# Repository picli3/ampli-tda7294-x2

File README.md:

# ampli-tda7294-x2

Amplificador de audio basado en **dos TDA7294**, pensado como una solución práctica para construir una etapa estéreo de potencia usando un integrado muy conocido en audio DIY.

## Propósito del proyecto
Este repositorio reúne el diseño electrónico y mecánico de una placa orientada a implementar un amplificador con **dos canales**, usando el TDA7294 como núcleo de cada etapa.

La idea principal del proyecto es ofrecer una base para:
- construir un amplificador estéreo
- reutilizar una topología conocida y fácil de conseguir
- integrar PCB, esquemático y soporte mecánico/disipación
- facilitar prototipado o fabricación de una etapa de audio casera o semiprofesional

## Qué incluye
- esquemáticos del amplificador
- diseño PCB en KiCad
- documentación exportada en PDF/HTML
- archivos mecánicos del disipador o soporte en FreeCAD

## Enfoque técnico
El TDA7294 es un integrado muy usado en amplificadores de audio por su simplicidad de implementación y buena potencia para aplicaciones domésticas, educativas o DIY. En este proyecto se usa por duplicado, lo que permite montar una etapa de dos canales sobre una misma base de diseño.

## Aplicaciones típicas
- amplificador estéreo DIY
- sistema de audio casero
- etapa de potencia para pruebas de laboratorio
- proyecto educativo de audio analógico

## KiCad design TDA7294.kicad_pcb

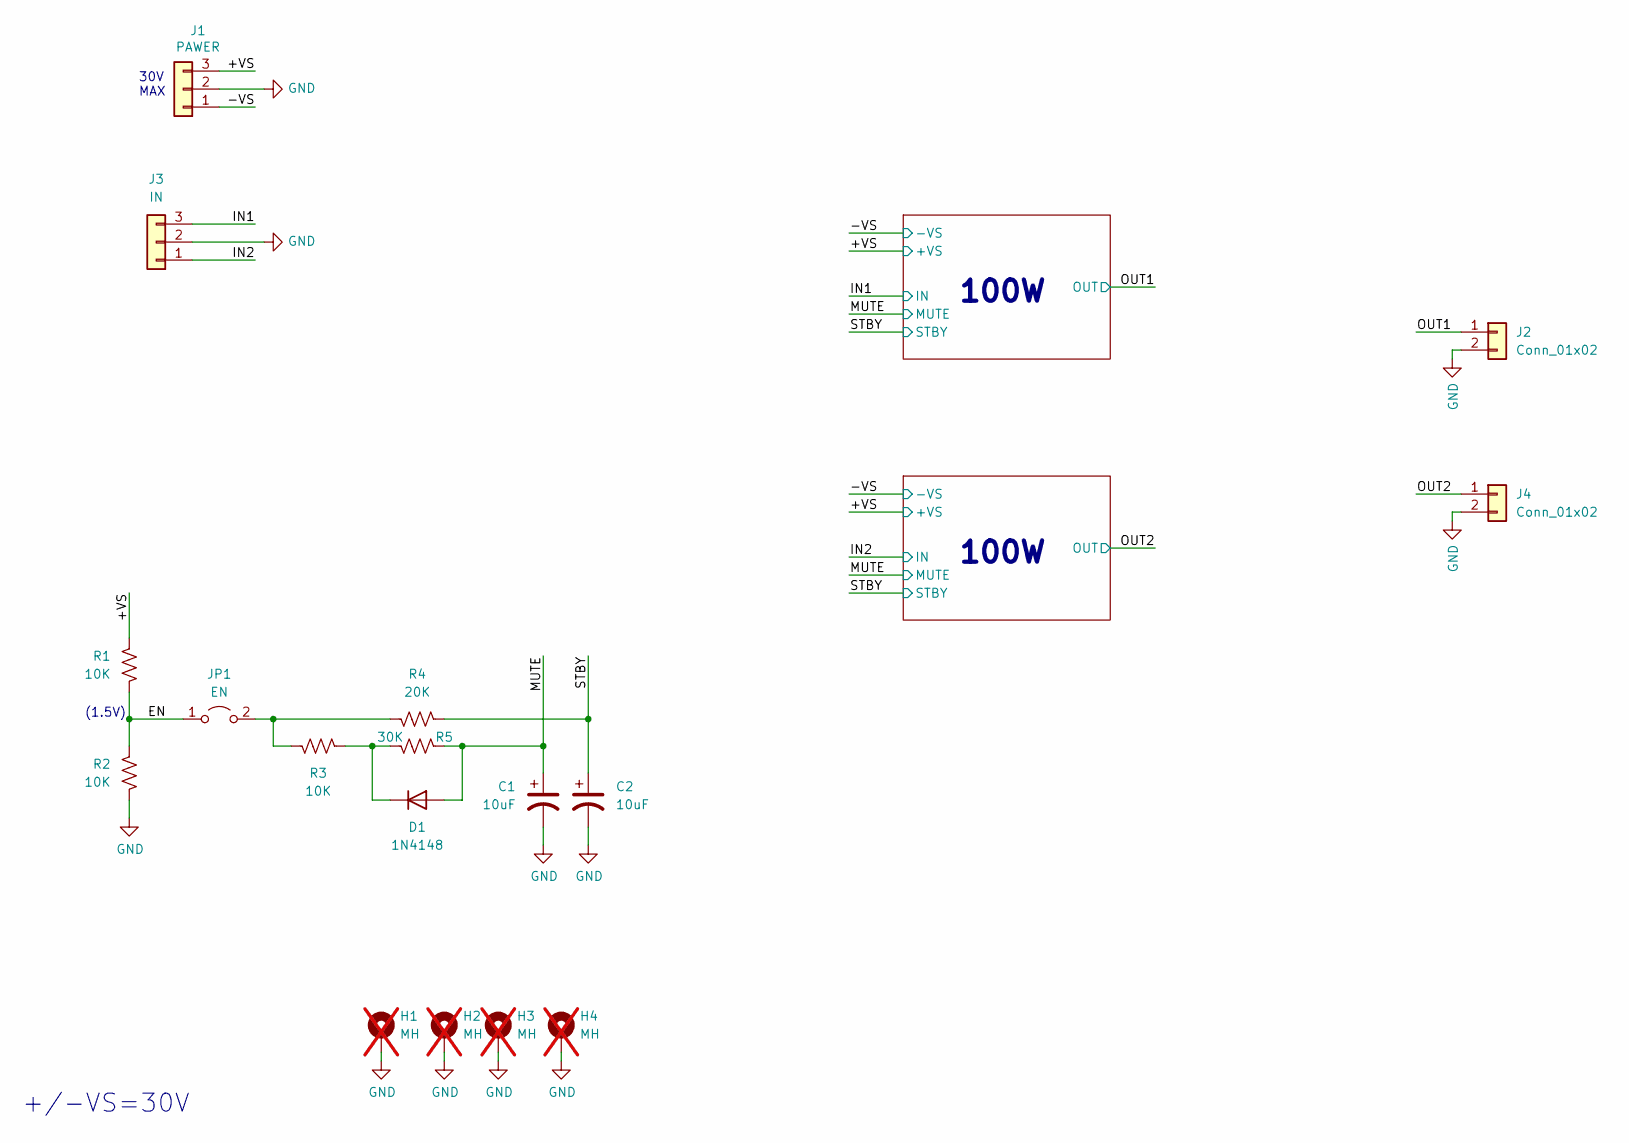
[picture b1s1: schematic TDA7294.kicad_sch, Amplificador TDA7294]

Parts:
C1, C2: 10uF; CP_Radial_D5.0mm_P2.50mm
D1: 1N4148; D_A-405_P10.16mm_Horizontal
H1, H2, H3, H4: MH; MountingHole_3.2mm_M3_DIN965_Pad; not fitted
J1: PAWER; Hirose_DF63M-3P-3.96DSA_1x03_P3.96mm_Vertical
J2, J4: Conn_01x02; Molex_KK-254_AE-6410-02A_1x02_P2.54mm_Vertical
J3: IN; Molex_KK-254_AE-6410-03A_1x03_P2.54mm_Vertical
JP1: EN; PinHeader_1x02_P2.54mm_Vertical
R1, R2, R3: 10K; R_Axial_DIN0207_L6.3mm_D2.5mm_P10.16mm_Horizontal
R4: 20K; R_Axial_DIN0207_L6.3mm_D2.5mm_P10.16mm_Horizontal
R5: 30K; R_Axial_DIN0207_L6.3mm_D2.5mm_P10.16mm_Horizontal

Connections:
/+VS: J1.3, R1.2; also elsewhere on the board
/-VS: J1.1; also elsewhere on the board
/EN: JP1.1 (A), R1.1, R2.2
/IN1: J3.3; also elsewhere on the board
/IN2: J3.1; also elsewhere on the board
/MUTE: C1.1, D1.2 (A), R5.1; also elsewhere on the board
/OUT1: J2.1; also elsewhere on the board
/OUT2: J4.1; also elsewhere on the board
/STBY: C2.1, R4.1; also elsewhere on the board
GND: C1.2, C2.2, H1.1, H2.1, H3.1, H4.1, J1.2, J2.2, J3.2, J4.2, R2.1; also elsewhere on the board
unnamed: D1.1 (K), R3.1, R5.2
unnamed: JP1.2 (B), R3.2, R4.2

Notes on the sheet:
100W
+/-VS=30V
(1.5V)
30V MAX

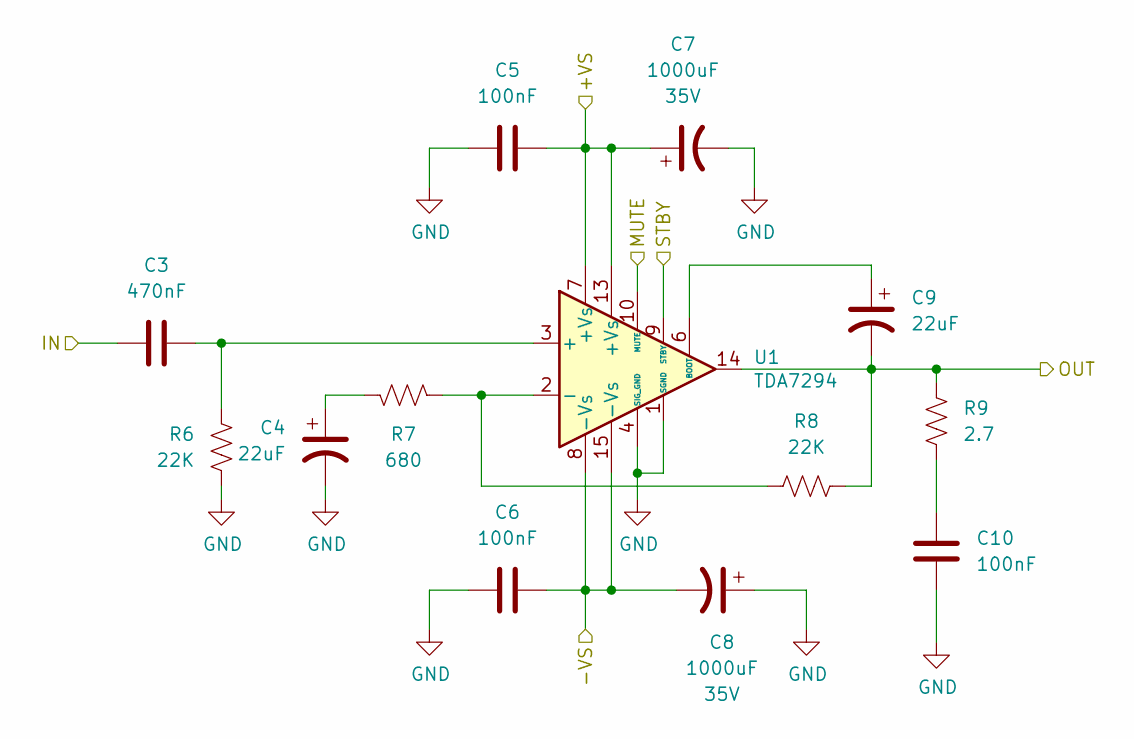
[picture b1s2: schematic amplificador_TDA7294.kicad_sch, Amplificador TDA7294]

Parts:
C3: 470nF; C_Disc_D4.3mm_W1.9mm_P5.00mm
C4, C9: 22uF; CP_Radial_D5.0mm_P2.50mm
C5, C6, C10: 100nF; C_Disc_D4.7mm_W2.5mm_P5.00mm; VOLTAGE 50V; Mfr. Part CC1H104ZC74D3F5O30MN; LCSC Part C254094
C7, C8: 1000uF; CP_Radial_D10.0mm_P5.00mm; VOLTAGE 35V; Mfr. Part ERR1VM102G20OT; LCSC Part C398835
R6, R8: 22K; R_Axial_DIN0207_L6.3mm_D2.5mm_P10.16mm_Horizontal
R7: 680; R_Axial_DIN0207_L6.3mm_D2.5mm_P10.16mm_Horizontal
R9: 2.7; R_Axial_DIN0411_L9.9mm_D3.6mm_P15.24mm_Horizontal
U1: TDA7294; TO-220-15_P2.54x2.54mm_StaggerOdd_Lead4.58mm_Vertical

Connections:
/+VS: C5.1, C7.1, U1.7 (+Vs), U1.13 (+Vs); also elsewhere on the board
/-VS: C6.1, C8.2, U1.8 (-Vs), U1.15 (-Vs); also elsewhere on the board
/IN1: C3.2; also elsewhere on the board
/MUTE: U1.10 (MUTE); also elsewhere on the board
/OUT1: C9.2, R8.1, R9.2, U1.14; also elsewhere on the board
/STBY: U1.9 (STBY); also elsewhere on the board
GND: C4.2, C5.2, C6.2, C7.2, C8.1, C10.1, R6.1, U1.1 (SGND), U1.4 (SIG_GND); also elsewhere on the board
unnamed: C4.1, R7.2
unnamed: C10.2, R9.1
unnamed: C3.1, R6.2, U1.3 (+)
unnamed: R7.1, R8.2, U1.2 (-)
unnamed: C9.1, U1.6 (BOOT)

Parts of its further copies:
C11: 470nF; C_Disc_D4.3mm_W1.9mm_P5.00mm
C12, C17: 22uF; CP_Radial_D5.0mm_P2.50mm
C13, C14, C18: 100nF; C_Disc_D4.7mm_W2.5mm_P5.00mm; VOLTAGE 50V; Mfr. Part CC1H104ZC74D3F5O30MN; LCSC Part C254094
C15, C16: 1000uF; CP_Radial_D10.0mm_P5.00mm; VOLTAGE 35V; Mfr. Part ERR1VM102G20OT; LCSC Part C398835
R10, R12: 22K; R_Axial_DIN0207_L6.3mm_D2.5mm_P10.16mm_Horizontal
R11: 680; R_Axial_DIN0207_L6.3mm_D2.5mm_P10.16mm_Horizontal
R13: 2.7; R_Axial_DIN0411_L9.9mm_D3.6mm_P15.24mm_Horizontal
U2: TDA7294; TO-220-15_P2.54x2.54mm_StaggerOdd_Lead4.58mm_Vertical

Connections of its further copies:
/+VS: C13.1, C15.1, U2.7 (+Vs), U2.13 (+Vs); also elsewhere on the board
/-VS: C14.1, C16.2, U2.8 (-Vs), U2.15 (-Vs); also elsewhere on the board
/IN2: C11.2; also elsewhere on the board
/MUTE: U2.10 (MUTE); also elsewhere on the board
/OUT2: C17.2, R12.1, R13.2, U2.14; also elsewhere on the board
/STBY: U2.9 (STBY); also elsewhere on the board
GND: C12.2, C13.2, C14.2, C15.2, C16.1, C18.1, R10.1, U2.1 (SGND), U2.4 (SIG_GND); also elsewhere on the board
unnamed: C12.1, R11.2
unnamed: C18.2, R13.1
unnamed: C11.1, R10.2, U2.3 (+)
unnamed: R11.1, R12.2, U2.2 (-)
unnamed: C17.1, U2.6 (BOOT)

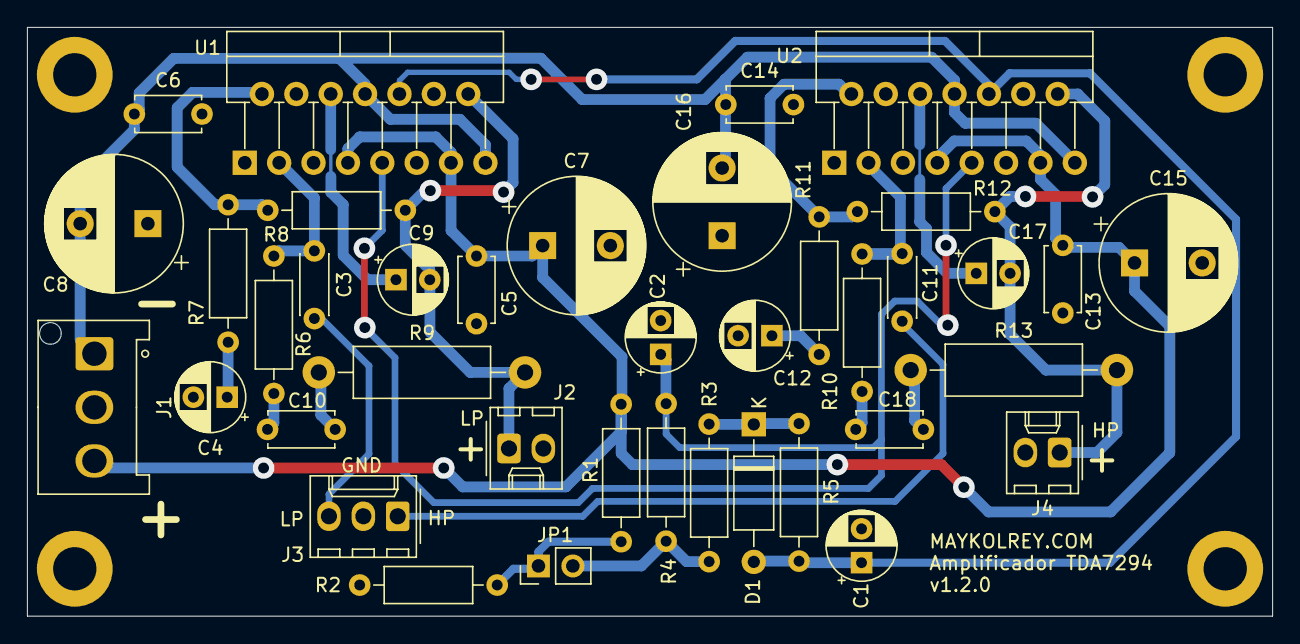
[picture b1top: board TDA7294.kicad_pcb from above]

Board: 2 copper layers, 92.0 x 43.5 mm, 43 parts (0 on the bottom side), 22 nets.

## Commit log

2022-06-05 enviado a fabricar
2022-12-08 agregando huecos para montaje
2023-12-14 eliminando archivos extras
2023-12-14 agregando git ignore mejorado
2023-12-17 completada version 1.1.0 con TDA al mismo lado
2024-02-05 add version puenteable y archivos en pdf
2024-03-16 mejorando los conectores
2026-04-29 Agrega README con descripción del proyecto
